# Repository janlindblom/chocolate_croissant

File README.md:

# The Chocolate Croissant

Yeah the name is stupid, I know.

This is a breakout board for when you want to fit a Raspberry Pi [34] B hat
onto a Raspberry Pi Pico or fit a Raspberry Pi Pico in something that expects a
full Raspberry Pi [34] B+.

The Raspberry Pi Pico W fits too of course.

## Pinout

The pinout might not be what you expect since the idea is to map function to
function rather than GPIO pin to pin.

By this I mean that the Pico I2C0 pins are mapped to the I<sup>2</sup>C pins of the
Raspberry Pi B+, SPI0 on the Pico is mapped to the SPI of the Raspberry Pi B+
and so on.

| Pin | Func             | Func             | Pin |
| :-- | :--------------- | :--------------- | --: |
| 1   | +3.3V            | +5V              | 2   |
| 3   | SDA0/GPIO4       | +5V              | 4   |
| 5   | SCL0/GPIO5       | GND              | 6   |
| 7   | GPIO6            | TX/GPIO0         | 8   |
| 9   | GND              | RX/GPIO1         | 10  |
| 11  | GPIO11           | SPI1_CS/GPIO13   | 12  |
| 13  | *TODO*           | GND              | 14  |
| 15  | GPIO20           | GPIO21           | 16  |
| 17  | +3.3V            | GPIO22           | 18  |
| 19  | SPI0_MOSI/GPIO19 | GND              | 20  |
| 21  | SPI0_MISO/GPIO16 | GPIO23           | 22  |
| 23  | SPI0_SCK/GPIO18  | SPI0_CS/GPIO17   | 24  |
| 25  | GND              | GPIO9            | 26  |
| 27  | SDA1/GPIO26      | SCL1/GPIO27      | 28  |
| 29  | GPIO7            | GND              | 30  |
| 31  | GPIO8            | PWM1A/GPIO2      | 32  |
| 33  | PWM1B/GPIO3      | GND              | 34  |
| 35  | SPI1_MISO/GPIO12 | GPIO10           | 36  |
| 37  | *TODO*           | SPI1_MOSI/GPIO12 | 38  |
| 39  | GND              | SPI1_SCK/GPIO14  | 40  |

There are two pins that are not currently connected to anything, these are
Raspberry Pi B+ pins `GPIO26` and `GPIO27`. They should obviously be connected,
the question is to what they should be connected. Maybe I need to rethink the
mapping of other stuff since I don't really have any more pins to connect from
the Pico.

### Special Breakouts

There are a couple of special breakouts avaiable:

- I<sup>2</sup>C - Four pin connector for general I<sup>2</sup>C devices
- SPI - Two SPI pin connectors:
  - Six pin SPI to fit SPI devices with six pins
  - Eight pin SPI to fit SPI devices with eight pins
- Qwiic/STEMMA QT - Two placements for Qwiic/STEMMA QT connectors:
  - I<sup>2</sup>C connected to I2C0 on the Pico
  - I<sup>2</sup>C connected to the debug pins

## Images

## TODO

- [ ] Connect Raspberry Pi B+ pins `GPIO26` and `GPIO27` (**NOTE:** To what??)
- [ ] Add a reset button somewhere and set it up to Pico pin `RUN` maybe(?)
- [x] Add some more "special" breakouts to enable attaching debug headers,
  displays, I<sup>2</sup>C/SPI stuff...
- [x] Describe any and all "special" breakouts, like the I<sup>2</sup>C mounting
  holes

## Future/Other Work

The `over_the_top` folder holds stuff related to the "over the top" version
which is basically a full blown RP2040 on a Raspberry Pi B+ board, it's based on
the KB2040 and the Raspberry Pi Pico datasheet and has a ton of tiny SMD
components that needs to be soldered to the board.

The idea is to use JLCPCB soldering services to have them all connected but that
requires some more research into which components they offer and such.

It's far from done and isn't really useful yet. Might finish it, might not. The
biggest hurdle is to get a wireless chip and antenna onto it, but I don't know
which chip that would be just yet. Could probably use the same as the Pico W,
but I think I would need to use a different antenna.

Anyway, there are some question marks regarding licenses for the chip and
antenna used on the Pico W that seems to indicate they are not quite free to use?

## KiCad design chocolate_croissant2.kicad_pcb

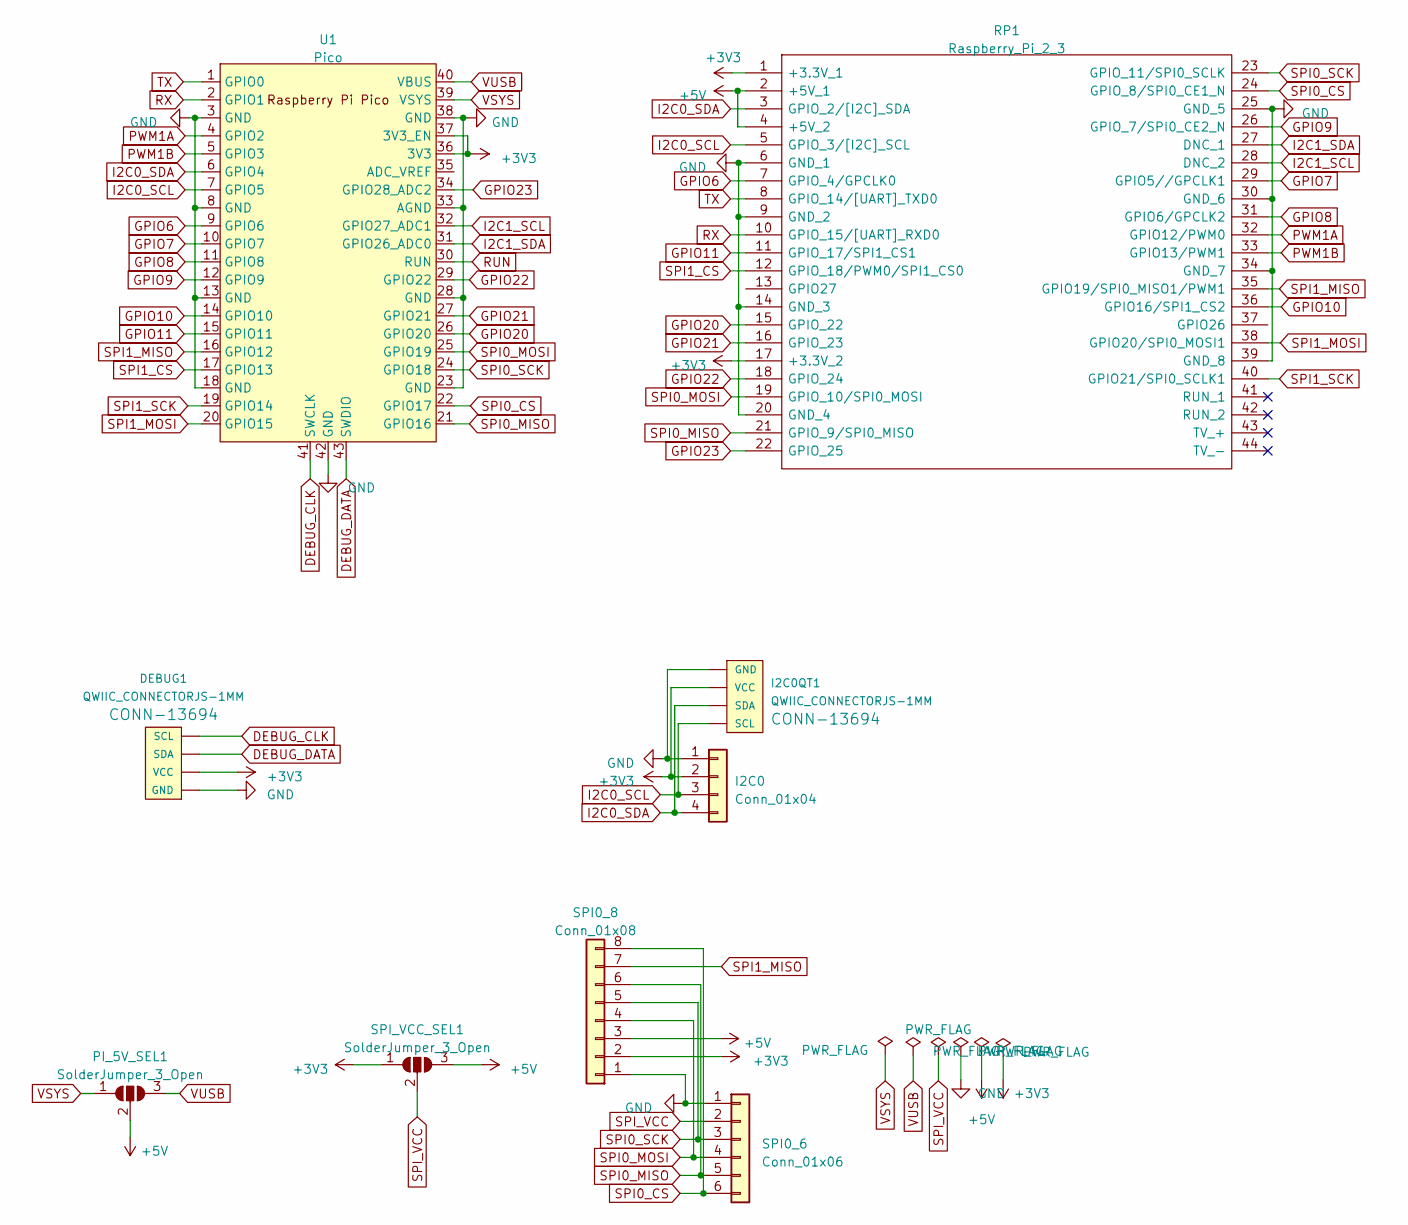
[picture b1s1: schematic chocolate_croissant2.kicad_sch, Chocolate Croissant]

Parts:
DEBUG1: QWIIC_CONNECTORJS-1MM; JST_SH_SM04B-SRSS-TB_1x04-1MP_P1.00mm_Horizontal
I2C0: Conn_01x04; PinHeader_1x04_P2.54mm_Vertical
I2C0QT1: QWIIC_CONNECTORJS-1MM; JST_SH_SM04B-SRSS-TB_1x04-1MP_P1.00mm_Horizontal
PI_5V_SEL1: SolderJumper_3_Open; SolderJumper-3_P1.3mm_Open_RoundedPad1.0x1.5mm_NumberLabels
RP1: Raspberry_Pi_2_3; raspberrypi_2_3; Manufacturer_Part_Number Raspberry Pi 2 or 3
SPI0_6: Conn_01x06; PinHeader_1x06_P2.54mm_Vertical
SPI0_8: Conn_01x08; PinHeader_1x08_P2.54mm_Vertical
SPI_VCC_SEL1: SolderJumper_3_Open; SolderJumper-3_P1.3mm_Open_RoundedPad1.0x1.5mm_NumberLabels
U1: Pico; RPi_Pico_SMD_TH

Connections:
+3V3: DEBUG1.2 (VCC), I2C0.2, I2C0QT1.2 (VCC), RP1.1 (+3.3V_1), RP1.17 (+3.3V_2), SPI0_8.2, SPI_VCC_SEL1.1 (A), U1.36 (3V3), U1.37 (3V3_EN)
+5V: PI_5V_SEL1.2 (C), RP1.2 (+5V_1), RP1.4 (+5V_2), SPI0_8.3, SPI_VCC_SEL1.3 (B)
DEBUG_CLK: DEBUG1.4 (SCL), U1.41 (SWCLK)
DEBUG_DATA: DEBUG1.3 (SDA), U1.43 (SWDIO)
GND: DEBUG1.1 (GND), I2C0.1, I2C0QT1.1 (GND), RP1.6 (GND_1), RP1.9 (GND_2), RP1.14 (GND_3), RP1.20 (GND_4), RP1.25 (GND_5), RP1.30 (GND_6), RP1.34 (GND_7), RP1.39 (GND_8), SPI0_6.1, SPI0_8.1, U1.3 (GND), U1.8 (GND), U1.13 (GND), U1.18 (GND), U1.23 (GND), U1.28 (GND), U1.33 (AGND), U1.38 (GND), U1.42 (GND)
GPIO6: RP1.7 (GPIO_4/GPCLK0), U1.9 (GPIO6)
GPIO7: RP1.29 (GPIO5//GPCLK1), U1.10 (GPIO7)
GPIO8: RP1.31 (GPIO6/GPCLK2), U1.11 (GPIO8)
GPIO9: RP1.26 (GPIO_7/SPI0_CE2_N), U1.12 (GPIO9)
GPIO10: RP1.36 (GPIO16/SPI1_CS2), U1.14 (GPIO10)
GPIO11: RP1.11 (GPIO_17/SPI1_CS1), U1.15 (GPIO11)
GPIO20: RP1.15 (GPIO_22), U1.26 (GPIO20)
GPIO21: RP1.16 (GPIO_23), U1.27 (GPIO21)
GPIO22: RP1.18 (GPIO_24), U1.29 (GPIO22)
GPIO23: RP1.22 (GPIO_25), U1.34 (GPIO28_ADC2)
I2C0_SCL: I2C0.3, I2C0QT1.4 (SCL), RP1.5 (GPIO_3/[I2C]_SCL), U1.7 (GPIO5)
I2C0_SDA: I2C0.4, I2C0QT1.3 (SDA), RP1.3 (GPIO_2/[I2C]_SDA), U1.6 (GPIO4)
I2C1_SCL: RP1.28 (DNC_2), U1.32 (GPIO27_ADC1)
I2C1_SDA: RP1.27 (DNC_1), U1.31 (GPIO26_ADC0)
PWM1A: RP1.32 (GPIO12/PWM0), U1.4 (GPIO2)
PWM1B: RP1.33 (GPIO13/PWM1), U1.5 (GPIO3)
RUN: U1.30 (RUN)
RX: RP1.10 (GPIO_15/[UART]_RXD0), U1.2 (GPIO1)
SPI0_CS: RP1.24 (GPIO_8/SPI0_CE1_N), SPI0_6.6, SPI0_8.8, U1.22 (GPIO17)
SPI0_MISO: RP1.21 (GPIO_9/SPI0_MISO), SPI0_6.5, SPI0_8.6, U1.21 (GPIO16)
SPI0_MOSI: RP1.19 (GPIO_10/SPI0_MOSI), SPI0_6.4, SPI0_8.4, U1.25 (GPIO19)
SPI0_SCK: RP1.23 (GPIO_11/SPI0_SCLK), SPI0_6.3, SPI0_8.5, U1.24 (GPIO18)
SPI1_CS: RP1.12 (GPIO_18/PWM0/SPI1_CS0), U1.17 (GPIO13)
SPI1_MISO: RP1.35 (GPIO19/SPI0_MISO1/PWM1), SPI0_8.7, U1.16 (GPIO12)
SPI1_MOSI: RP1.38 (GPIO20/SPI0_MOSI1), U1.20 (GPIO15)
SPI1_SCK: RP1.40 (GPIO21/SPI0_SCLK1), U1.19 (GPIO14)
SPI_VCC: SPI0_6.2, SPI_VCC_SEL1.2 (C)
TX: RP1.8 (GPIO_14/[UART]_TXD0), U1.1 (GPIO0)
VSYS: PI_5V_SEL1.1 (A), U1.39 (VSYS)
VUSB: PI_5V_SEL1.3 (B), U1.40 (VBUS)

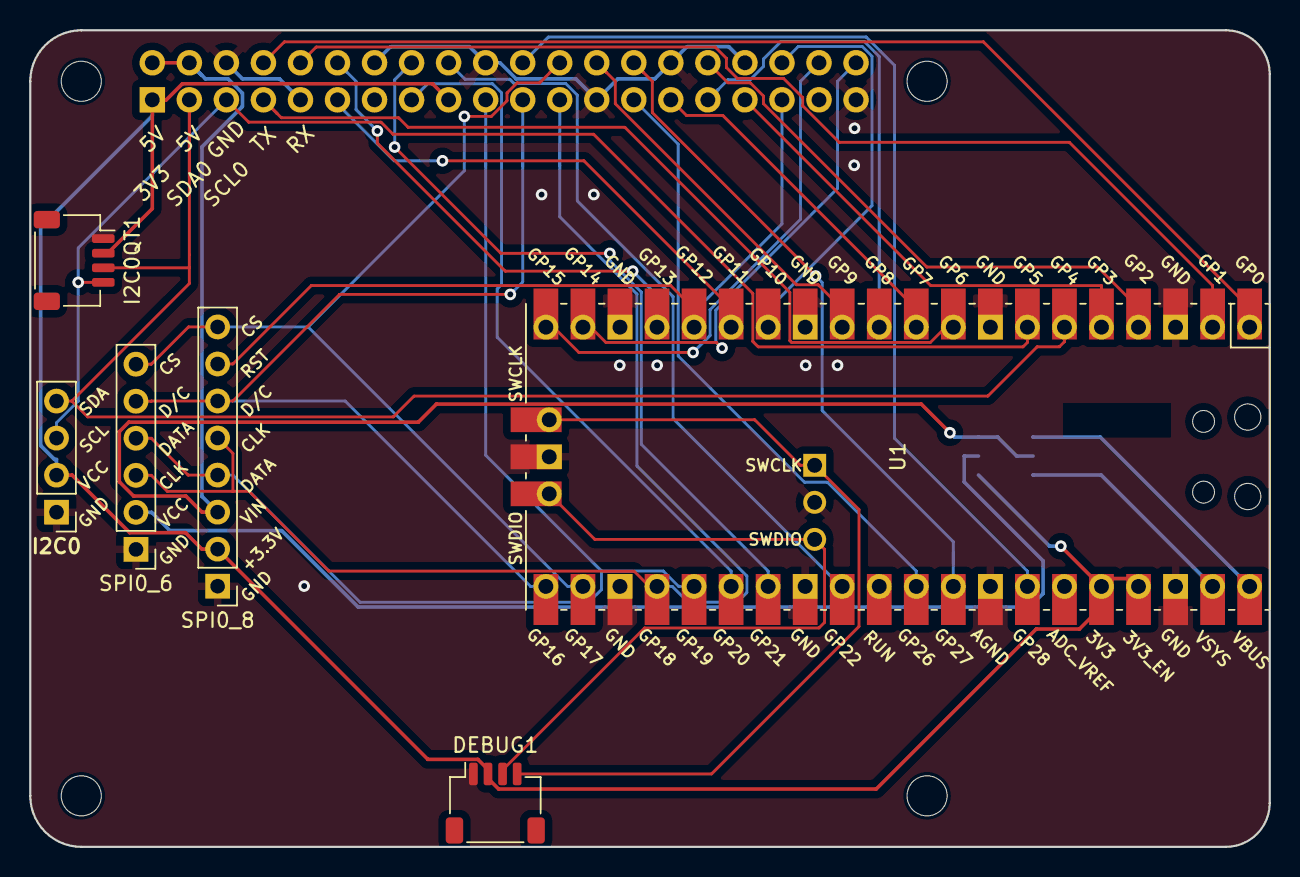
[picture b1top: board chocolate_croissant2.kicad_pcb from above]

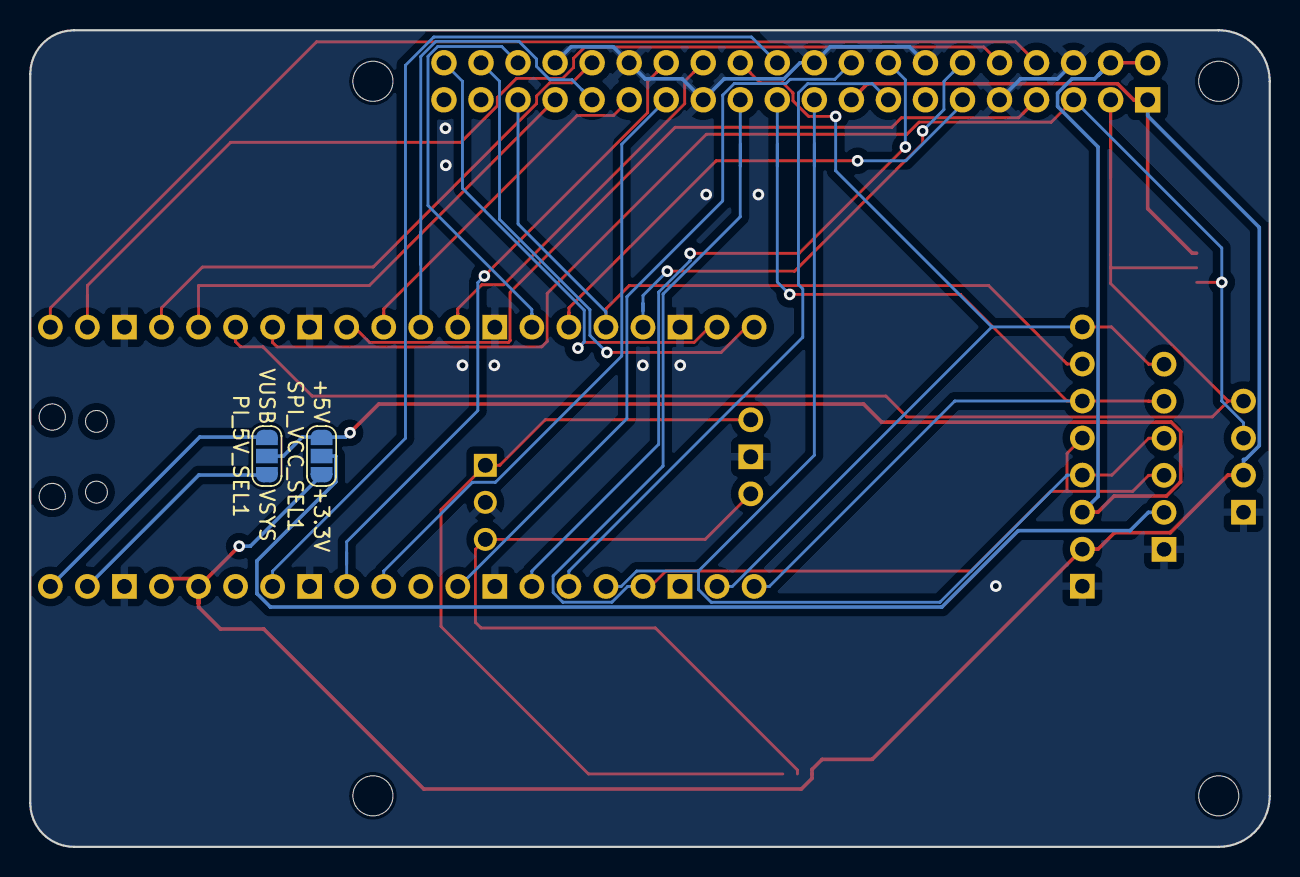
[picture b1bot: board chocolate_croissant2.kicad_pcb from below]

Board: 2 copper layers, 85.0 x 56.0 mm, 9 parts (2 on the bottom side), 34 nets.

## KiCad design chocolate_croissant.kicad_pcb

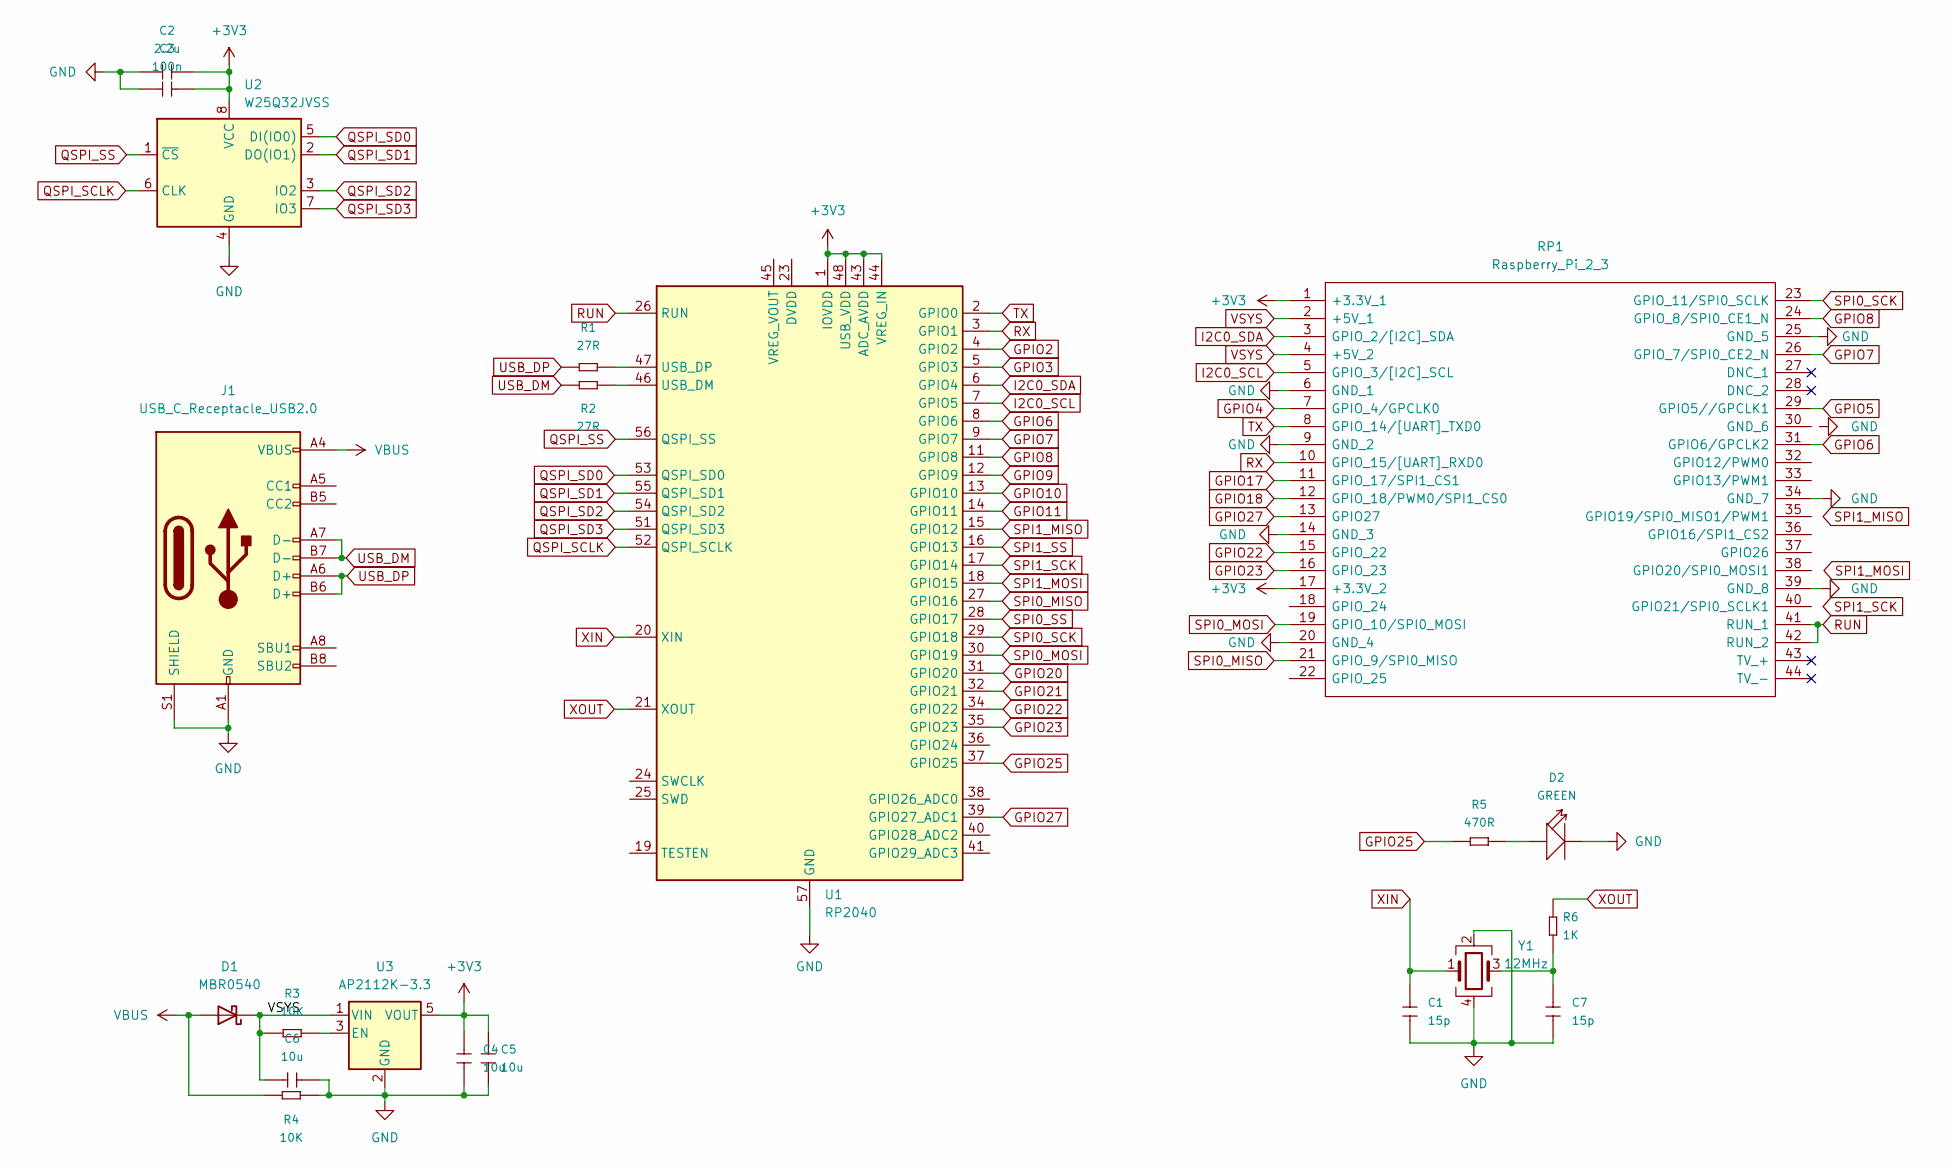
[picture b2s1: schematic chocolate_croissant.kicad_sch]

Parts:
C1, C7: 15p; C_1206_3216Metric_Pad1.33x1.80mm_HandSolder; MPN GRM31CR60J107ME39L
C2: 2.2u; C_0805_2012Metric_Pad1.18x1.45mm_HandSolder; MPN GRM31CR60J107ME39L
C3: 100n; C_0805_2012Metric_Pad1.18x1.45mm_HandSolder; MPN GRM31CR60J107ME39L
C4, C5, C6: 10u; C_1206_3216Metric_Pad1.33x1.80mm_HandSolder; MPN GRM31CR60J107ME39L
D1: MBR0540; D_SOD-123
D2: GREEN; LED_0805_2012Metric_Pad1.15x1.40mm_HandSolder; MPN 17-215SYGC_S530-E2_TR8
J1: USB_C_Receptacle_USB2.0; USB_C_Receptacle_Palconn_UTC16-G
R1, R2: 27R; R_0805_2012Metric_Pad1.20x1.40mm_HandSolder; MPN RC0603FR-0720KL
R3, R4: 10K; R_0603_1608Metric_Pad0.98x0.95mm_HandSolder; MPN RC0603FR-0720KL
R5: 470R; R_0603_1608Metric_Pad0.98x0.95mm_HandSolder; MPN RC0603FR-0720KL
R6: 1K; R_0603_1608Metric_Pad0.98x0.95mm_HandSolder; MPN RC0603FR-0720KL
RP1: Raspberry_Pi_2_3; raspberrypi_2_3; Manufacturer_Part_Number Raspberry Pi 2 or 3
U1: RP2040; QFN-56-1EP_7x7mm_P0.4mm_EP3.2x3.2mm
U2: W25Q32JVSS; SOIC-8_5.23x5.23mm_P1.27mm
U3: AP2112K-3.3; SOT-23-5
Y1: 12MHz; Crystal_SMD_0603-4Pin_6.0x3.5mm_HandSoldering

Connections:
+3V3: C2.2, C3.2, C4.1, C5.1, RP1.1 (+3.3V_1), RP1.17 (+3.3V_2), U1.1 (IOVDD), U1.10 (IOVDD), U1.22 (IOVDD), U1.33 (IOVDD), U1.42 (IOVDD), U1.43 (ADC_AVDD), U1.44 (VREG_IN), U1.48 (USB_VDD), U1.49 (IOVDD), U2.8 (VCC), U3.5 (VOUT)
GND: C1.1, C2.1, C3.1, C4.2, C5.2, C6.2, C7.1, D2.2 (-), J1.A1 (GND), J1.A12 (GND), J1.B1 (GND), J1.B12 (GND), J1.S1 (SHIELD), R4.2, RP1.6 (GND_1), RP1.9 (GND_2), RP1.14 (GND_3), RP1.20 (GND_4), RP1.25 (GND_5), RP1.34 (GND_7), RP1.39 (GND_8), U1.57 (GND), U2.4 (GND), U3.2 (GND), Y1.2, Y1.4
GPIO2: U1.4 (GPIO2)
GPIO3: U1.5 (GPIO3)
GPIO4: RP1.7 (GPIO_4/GPCLK0)
GPIO5: RP1.29 (GPIO5//GPCLK1)
GPIO6: RP1.31 (GPIO6/GPCLK2), U1.8 (GPIO6)
GPIO7: RP1.26 (GPIO_7/SPI0_CE2_N), U1.9 (GPIO7)
GPIO8: RP1.24 (GPIO_8/SPI0_CE1_N), U1.11 (GPIO8)
GPIO9: U1.12 (GPIO9)
GPIO10: U1.13 (GPIO10)
GPIO11: U1.14 (GPIO11)
GPIO17: RP1.11 (GPIO_17/SPI1_CS1)
GPIO18: RP1.12 (GPIO_18/PWM0/SPI1_CS0)
GPIO20: U1.31 (GPIO20)
GPIO21: U1.32 (GPIO21)
GPIO22: RP1.15 (GPIO_22), U1.34 (GPIO22)
GPIO23: RP1.16 (GPIO_23), U1.35 (GPIO23)
GPIO25: R5.1, U1.37 (GPIO25)
GPIO27: RP1.13 (GPIO27), U1.39 (GPIO27_ADC1)
I2C0_SCL: RP1.5 (GPIO_3/[I2C]_SCL), U1.7 (GPIO5)
I2C0_SDA: RP1.3 (GPIO_2/[I2C]_SDA), U1.6 (GPIO4)
unnamed: C7.2, R6.1, Y1.3
unnamed: D2.1 (+), R5.2
unnamed: R3.2, U3.3 (EN)
unnamed: U1.23 (DVDD), U1.50 (DVDD)
unnamed: R2.2, U1.46 (USB_DM)
unnamed: R1.2, U1.47 (USB_DP)
QSPI_SCLK: U1.52 (QSPI_SCLK), U2.6 (CLK)
QSPI_SD0: U1.53 (QSPI_SD0), U2.5 (DI(IO0))
QSPI_SD1: U1.55 (QSPI_SD1), U2.2 (DO(IO1))
QSPI_SD2: U1.54 (QSPI_SD2), U2.3 (IO2)
QSPI_SD3: U1.51 (QSPI_SD3), U2.7 (IO3)
QSPI_SS: U1.56 (QSPI_SS), U2.1 (~CS)
RUN: RP1.41 (RUN_1), RP1.42 (RUN_2), U1.26 (RUN)
RX: RP1.10 (GPIO_15/[UART]_RXD0), U1.3 (GPIO1)
SPI0_MISO: RP1.21 (GPIO_9/SPI0_MISO), U1.27 (GPIO16)
SPI0_MOSI: RP1.19 (GPIO_10/SPI0_MOSI), U1.30 (GPIO19)
SPI0_SCK: RP1.23 (GPIO_11/SPI0_SCLK), U1.29 (GPIO18)
SPI0_SS: U1.28 (GPIO17)
SPI1_MISO: U1.15 (GPIO12)
SPI1_MOSI: U1.18 (GPIO15)
SPI1_SCK: U1.17 (GPIO14)
SPI1_SS: U1.16 (GPIO13)
TX: RP1.8 (GPIO_14/[UART]_TXD0), U1.2 (GPIO0)
USB_DM: J1.A7 (D-), J1.B7 (D-), R2.1
USB_DP: J1.A6 (D+), J1.B6 (D+), R1.1
VBUS: D1.2 (A), J1.A4 (VBUS), J1.A9 (VBUS), J1.B4 (VBUS), J1.B9 (VBUS), R4.1
VSYS: C6.1, D1.1 (K), R3.1, RP1.2 (+5V_1), RP1.4 (+5V_2), U3.1 (VIN)
XIN: C1.2, U1.20 (XIN), Y1.1
XOUT: R6.2, U1.21 (XOUT)

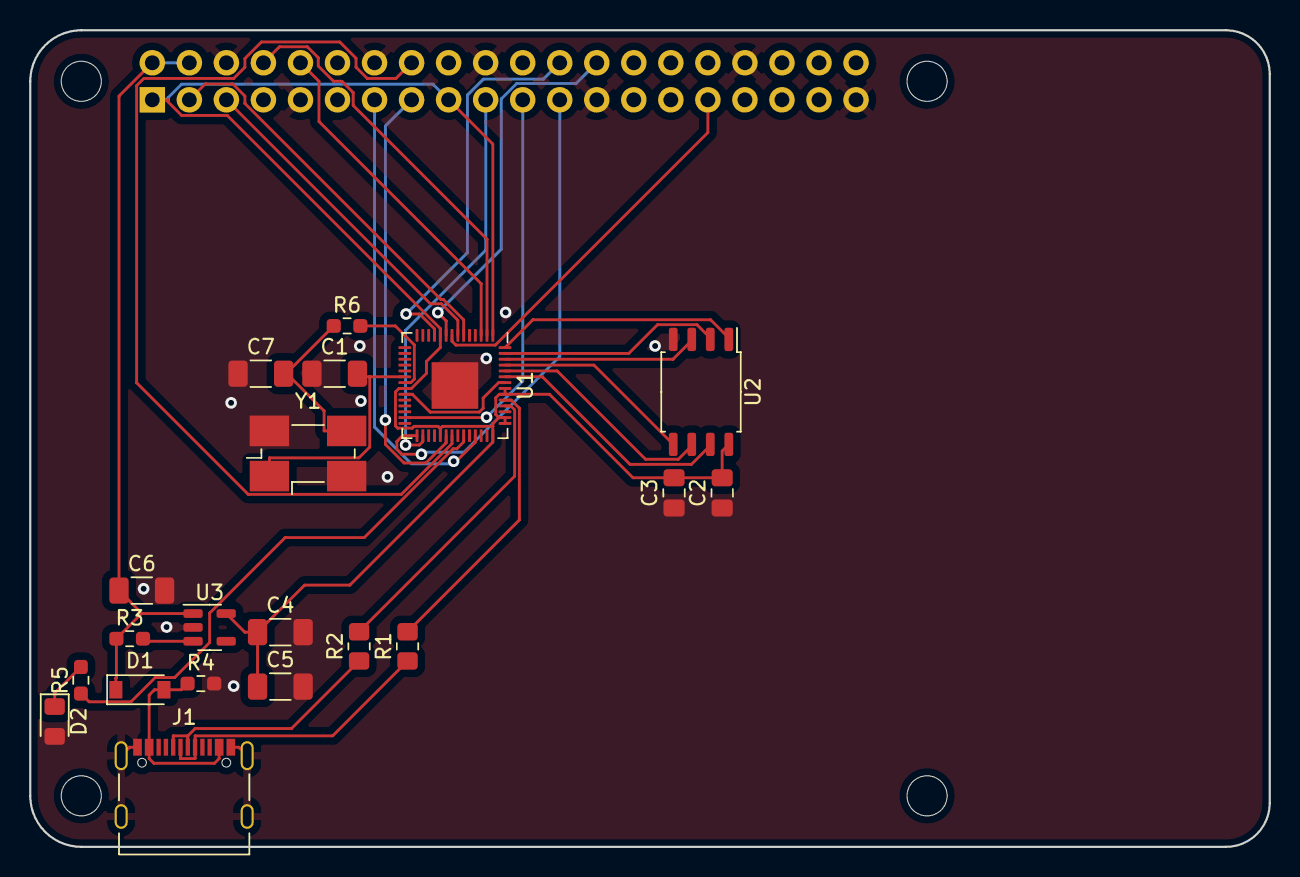
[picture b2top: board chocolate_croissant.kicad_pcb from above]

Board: 2 copper layers, 85.0 x 56.0 mm, 21 parts (0 on the bottom side), 34 nets.

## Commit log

2023-04-05 Initial commit, work in progress.
2023-04-05 Describe better what this thing is.
2023-04-05 Image of the back of the PCB added to README.
2023-04-06 SPI breakouts and new images.
2023-04-07 Cleaning up the files a bit.
2023-04-07 Adding some more stuff, more documentation in the README etc.
2023-04-10 KiCad 7 plus local footprints and symbols.
